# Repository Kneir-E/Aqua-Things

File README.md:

- **Aqua_Things_V2**
  - Arduino IDE platform  
  - Contains the latest version of the Main Device contents *(this is the latest that I can find, I lost copy to the actual final version)*
- **ESP8266_Calibration-Module**
  - Arduino IDE platform  
  - Contains the code for the Calibration Module
- **KiCad Files**
  - **3.1) ESP_Board_Test**  
    - KiCad Schematics for the main board of the device
  - **3.2) ESP8266_Calib_Module**  
    - KiCad Schematics for the calibration module board
  - **3.3) KiCad Extras-Libraries-etc**  
    - Libraries used for the creation of 3.1 and 3.2
- **Ignore the rest of the folders**
- **4) Old Version** → Ignore
- **5) Helper for testing - Lux-Web** → Ignore
- **6) Helper for testing - Temperature-Web** → Ignore

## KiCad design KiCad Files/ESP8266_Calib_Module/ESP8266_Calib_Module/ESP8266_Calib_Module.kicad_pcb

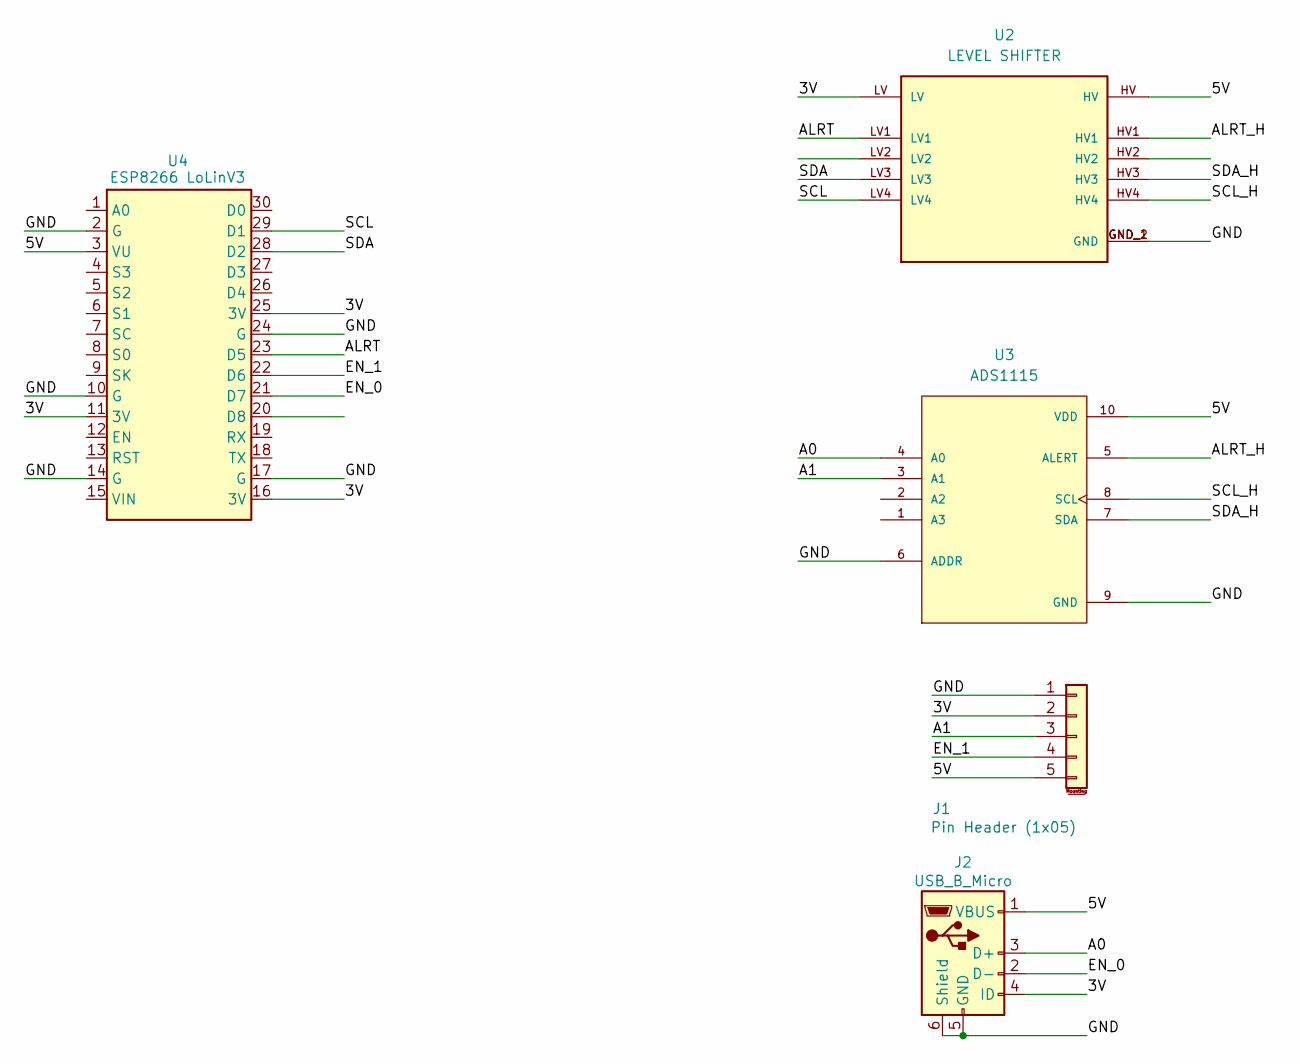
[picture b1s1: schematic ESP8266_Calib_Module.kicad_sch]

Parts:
J1: Pin Header (1x05); PinHeader_1x05_P2.54mm_Vertical
J2: USB_B_Micro; USB_Micro-B_Amphenol_10118194_Horizontal
U2: LEVEL SHIFTER; CONV_BOB-12009; PARTREV 01
U3: ADS1115; MODULE_ZC261500; PARTREV NA
U4: ESP8266 LoLinV3; NodeMCU-LoLinV3

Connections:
/3V: J1.2, J2.4 (ID), U2.LV, U4.11 (3V), U4.16 (3V), U4.25 (3V)
/5V: J1.5, J2.1 (VBUS), U2.HV, U3.10 (VDD), U4.3 (VU)
/A0: J2.3 (D+), U3.4 (A0)
/A1: J1.3, U3.3 (A1)
/ALRT: U2.LV1, U4.23 (D5)
/ALRT_H: U2.HV1, U3.5 (ALERT)
/EN_0: J2.2 (D-), U4.21 (D7)
/EN_1: J1.4, U4.22 (D6)
/GND: J1.1, J2.5 (GND), J2.6 (Shield), U2.GND_1 (GND), U2.GND_2 (GND), U3.6 (ADDR), U3.9 (GND), U4.2 (G), U4.10 (G), U4.14 (G), U4.17 (G), U4.24 (G)
/SCL: U2.LV4, U4.29 (D1)
/SCL_H: U2.HV4, U3.8 (SCL)
/SDA: U2.LV3, U4.28 (D2)
/SDA_H: U2.HV3, U3.7 (SDA)

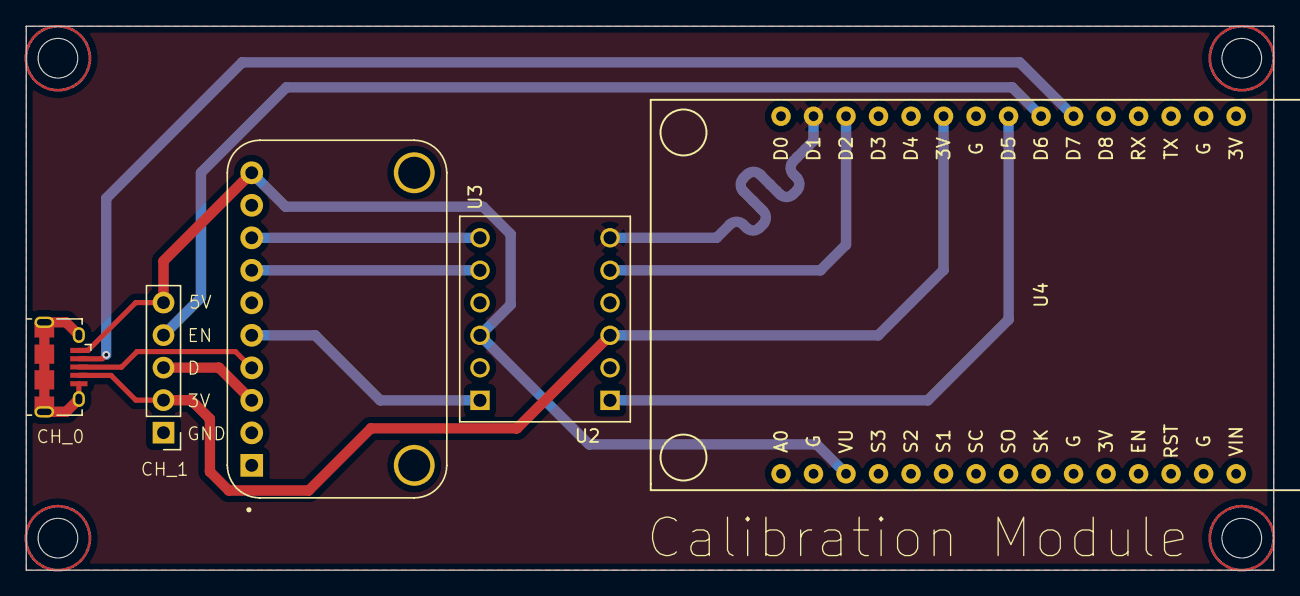
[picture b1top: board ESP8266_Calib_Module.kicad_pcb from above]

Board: 2 copper layers, 97.5 x 42.5 mm, 5 parts (0 on the bottom side), 13 nets.

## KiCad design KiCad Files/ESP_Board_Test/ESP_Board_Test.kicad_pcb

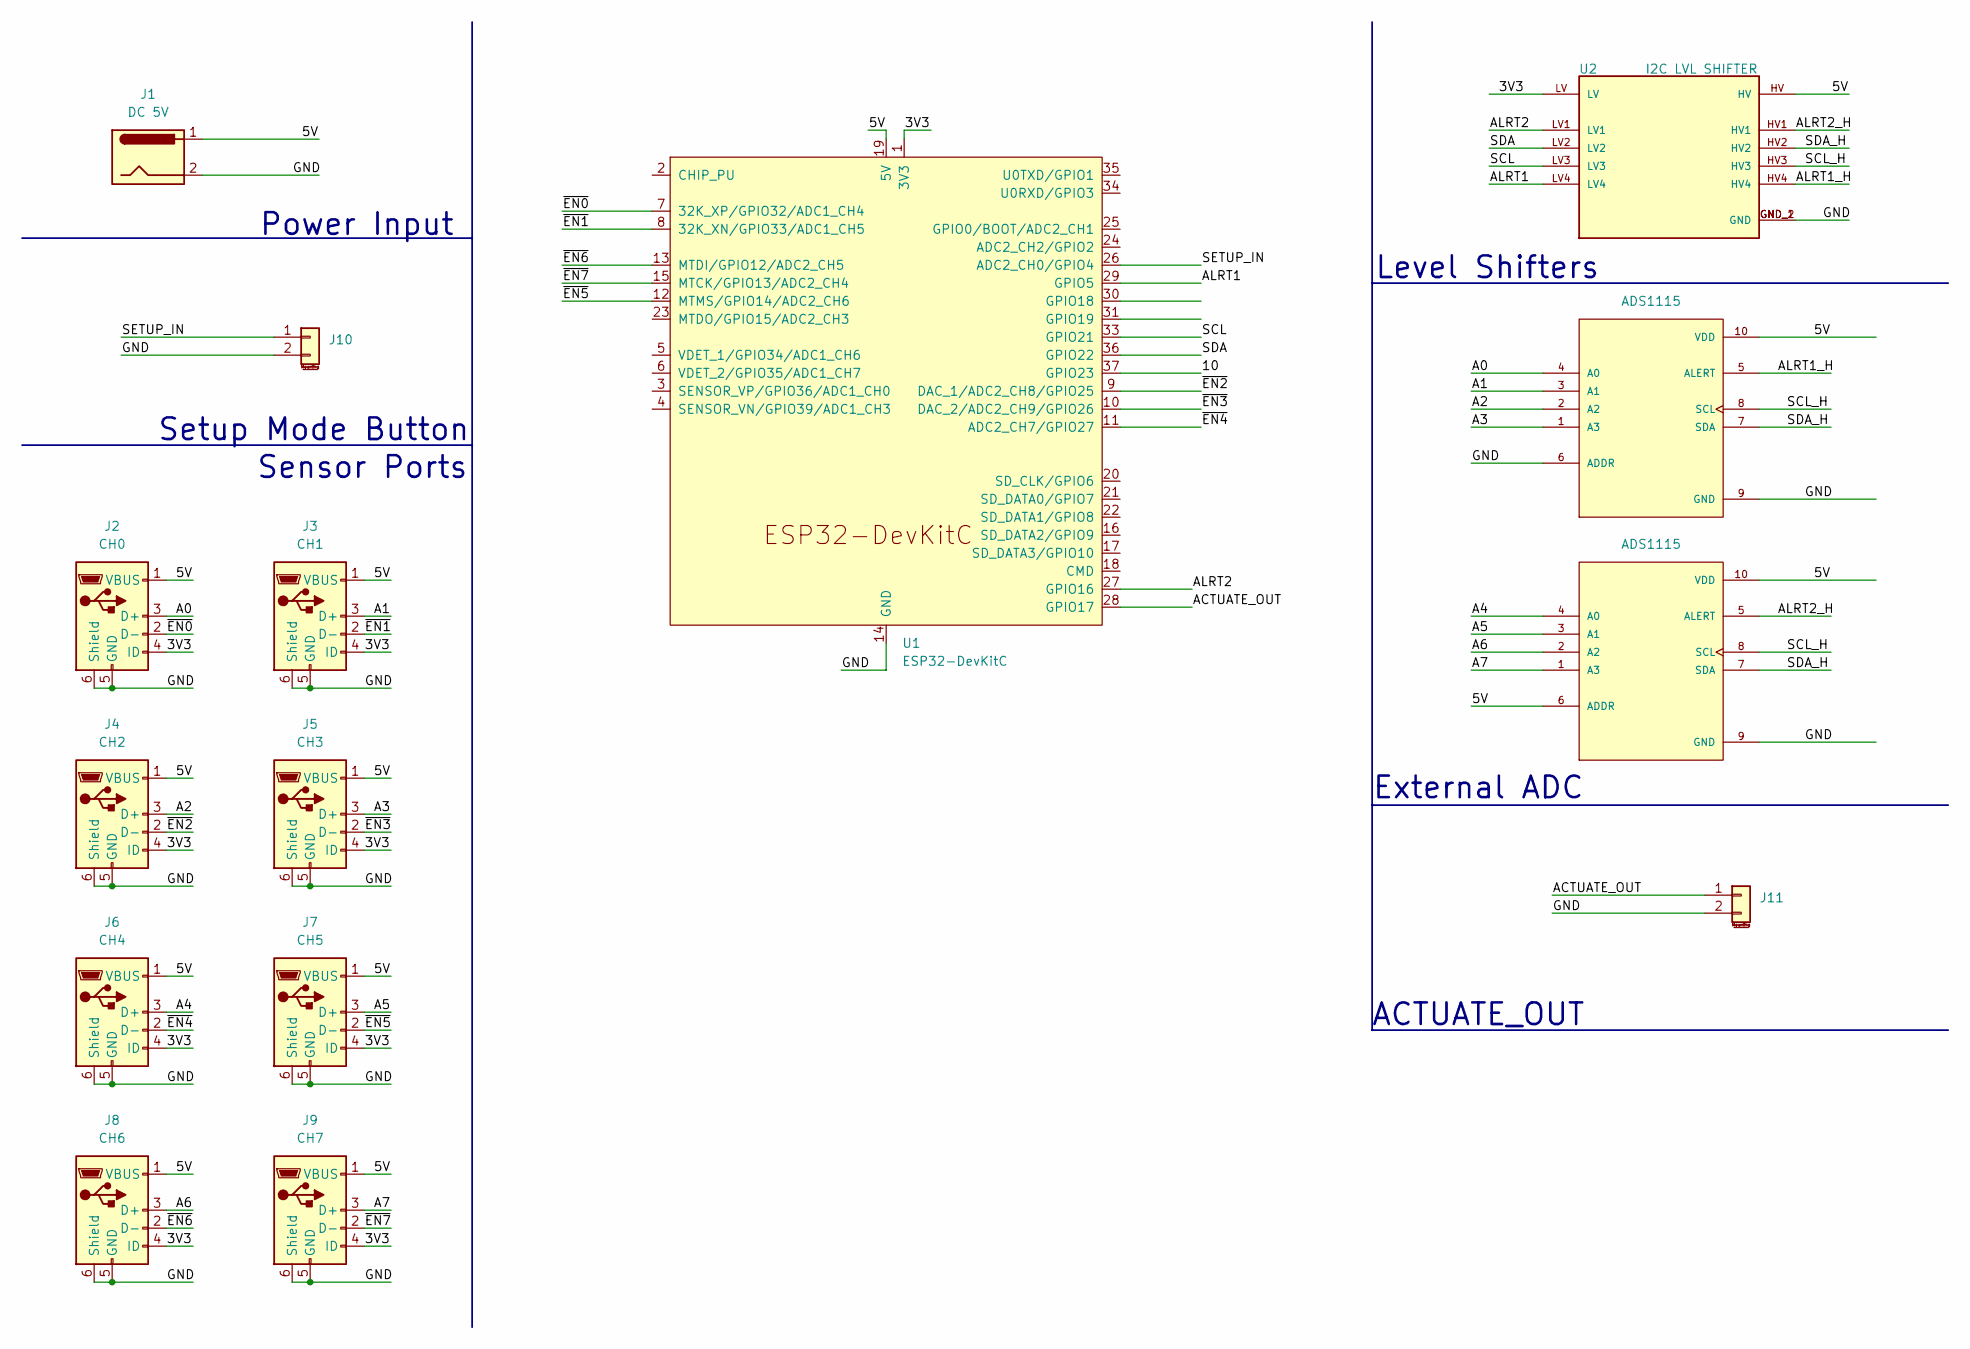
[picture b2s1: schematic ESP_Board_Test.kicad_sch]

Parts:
J1: DC 5V; BarrelJack_Horizontal
J2: CH0; USB_Micro-B_Amphenol_10118194_Horizontal
J3: CH1; USB_Micro-B_Amphenol_10118194_Horizontal
J4: CH2; USB_Micro-B_Amphenol_10118194_Horizontal
J5: CH3; USB_Micro-B_Amphenol_10118194_Horizontal
J6: CH4; USB_Micro-B_Amphenol_10118194_Horizontal
J7: CH5; USB_Micro-B_Amphenol_10118194_Horizontal
J8: CH6; USB_Micro-B_Amphenol_10118194_Horizontal
J9: CH7; USB_Micro-B_Amphenol_10118194_Horizontal
J10, J11: Pin Header; PinHeader_1x02_P2.54mm_Vertical
U1: ESP32-DevKitC
U2: I2C LVL SHIFTER; CONV_BOB-12009; PARTREV 01
U4, U5: ADS1115; MODULE_ZC261500; PARTREV NA

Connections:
/3V3: J2.4 (ID), J3.4 (ID), J4.4 (ID), J5.4 (ID), J6.4 (ID), J7.4 (ID), J8.4 (ID), J9.4 (ID), U1.1 (3V3), U2.LV
/5V: J1.1, J2.1 (VBUS), J3.1 (VBUS), J4.1 (VBUS), J5.1 (VBUS), J6.1 (VBUS), J7.1 (VBUS), J8.1 (VBUS), J9.1 (VBUS), U1.19 (5V), U2.HV, U4.10 (VDD), U5.6 (ADDR), U5.10 (VDD)
/10: U1.37 (GPIO23)
/A0: J2.3 (D+), U4.4 (A0)
/A1: J3.3 (D+), U4.3 (A1)
/A2: J4.3 (D+), U4.2 (A2)
/A3: J5.3 (D+), U4.1 (A3)
/A4: J6.3 (D+), U5.4 (A0)
/A5: J7.3 (D+), U5.3 (A1)
/A6: J8.3 (D+), U5.2 (A2)
/A7: J9.3 (D+), U5.1 (A3)
/ACTUATE_OUT: J11.1, U1.28 (GPIO17)
/ALRT1: U1.29 (GPIO5), U2.LV4
/ALRT1_H: U2.HV4, U4.5 (ALERT)
/ALRT2: U1.27 (GPIO16), U2.LV1
/ALRT2_H: U2.HV1, U5.5 (ALERT)
/GND: J1.2, J2.5 (GND), J2.6 (Shield), J3.5 (GND), J3.6 (Shield), J4.5 (GND), J4.6 (Shield), J5.5 (GND), J5.6 (Shield), J6.5 (GND), J6.6 (Shield), J7.5 (GND), J7.6 (Shield), J8.5 (GND), J8.6 (Shield), J9.5 (GND), J9.6 (Shield), J10.2, J11.2, U1.14 (GND), U1.32 (GND), U1.38 (GND), U2.GND_1 (GND), U2.GND_2 (GND), U4.6 (ADDR), U4.9 (GND), U5.9 (GND)
/SCL: U1.33 (GPIO21), U2.LV3
/SCL_H: U2.HV3, U4.8 (SCL), U5.8 (SCL)
/SDA: U1.36 (GPIO22), U2.LV2
/SDA_H: U2.HV2, U4.7 (SDA), U5.7 (SDA)
/SETUP_IN: J10.1, U1.26 (ADC2_CH0/GPIO4)
/~EN0: J2.2 (D-), U1.7 (32K_XP/GPIO32/ADC1_CH4)
/~EN1: J3.2 (D-), U1.8 (32K_XN/GPIO33/ADC1_CH5)
/~EN2: J4.2 (D-), U1.9 (DAC_1/ADC2_CH8/GPIO25)
/~EN3: J5.2 (D-), U1.10 (DAC_2/ADC2_CH9/GPIO26)
/~EN4: J6.2 (D-), U1.11 (ADC2_CH7/GPIO27)
/~EN5: J7.2 (D-), U1.12 (MTMS/GPIO14/ADC2_CH6)
/~EN6: J8.2 (D-), U1.13 (MTDI/GPIO12/ADC2_CH5)
/~EN7: J9.2 (D-), U1.15 (MTCK/GPIO13/ADC2_CH4)

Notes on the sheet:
Sensor Ports
Power Input
ACTUATE_OUT
External ADC
Level Shifters
Setup Mode Button

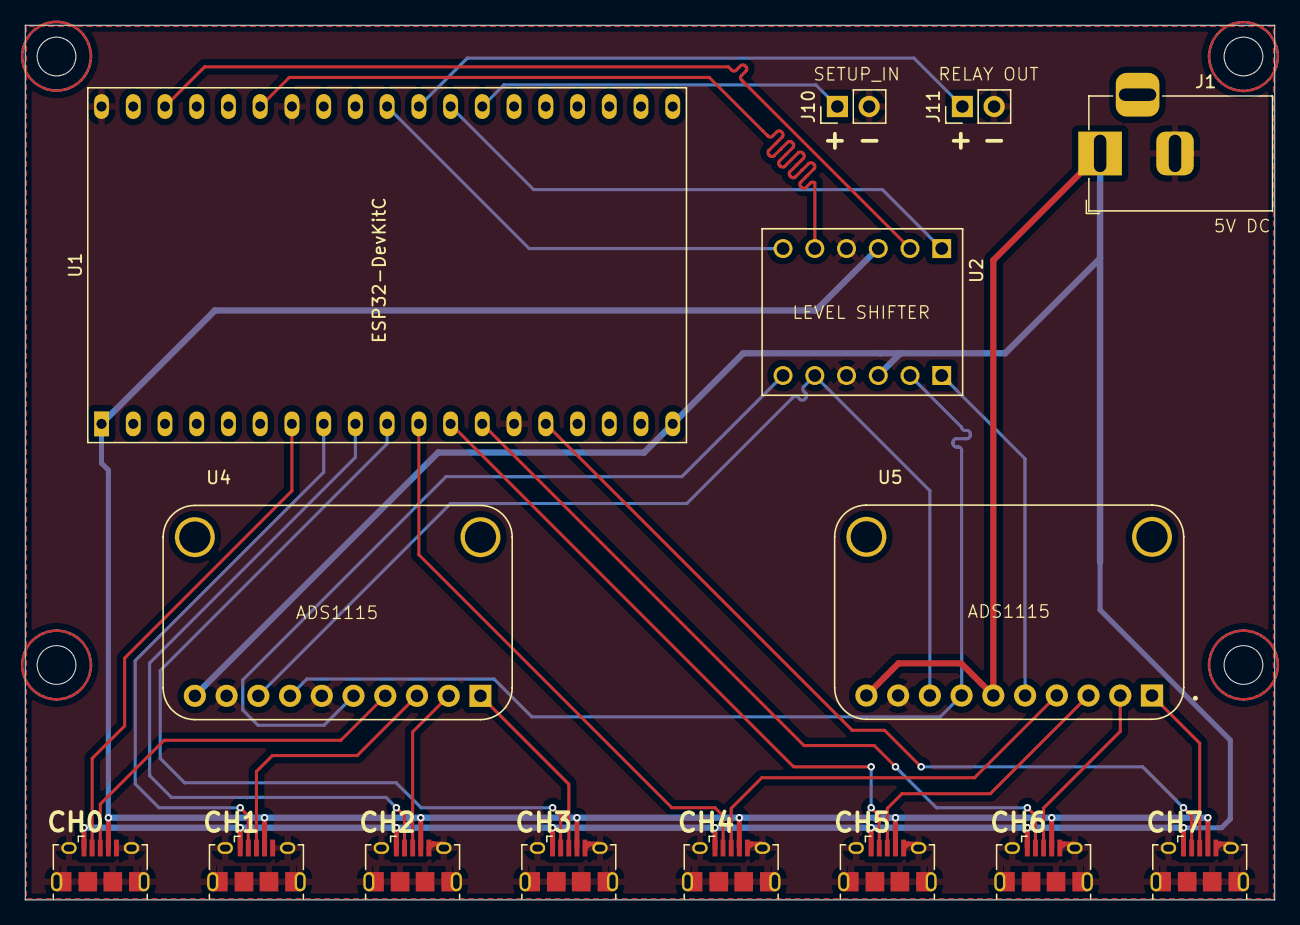
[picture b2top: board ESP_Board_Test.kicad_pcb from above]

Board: 2 copper layers, 100.0 x 70.0 mm, 15 parts (0 on the bottom side), 29 nets.

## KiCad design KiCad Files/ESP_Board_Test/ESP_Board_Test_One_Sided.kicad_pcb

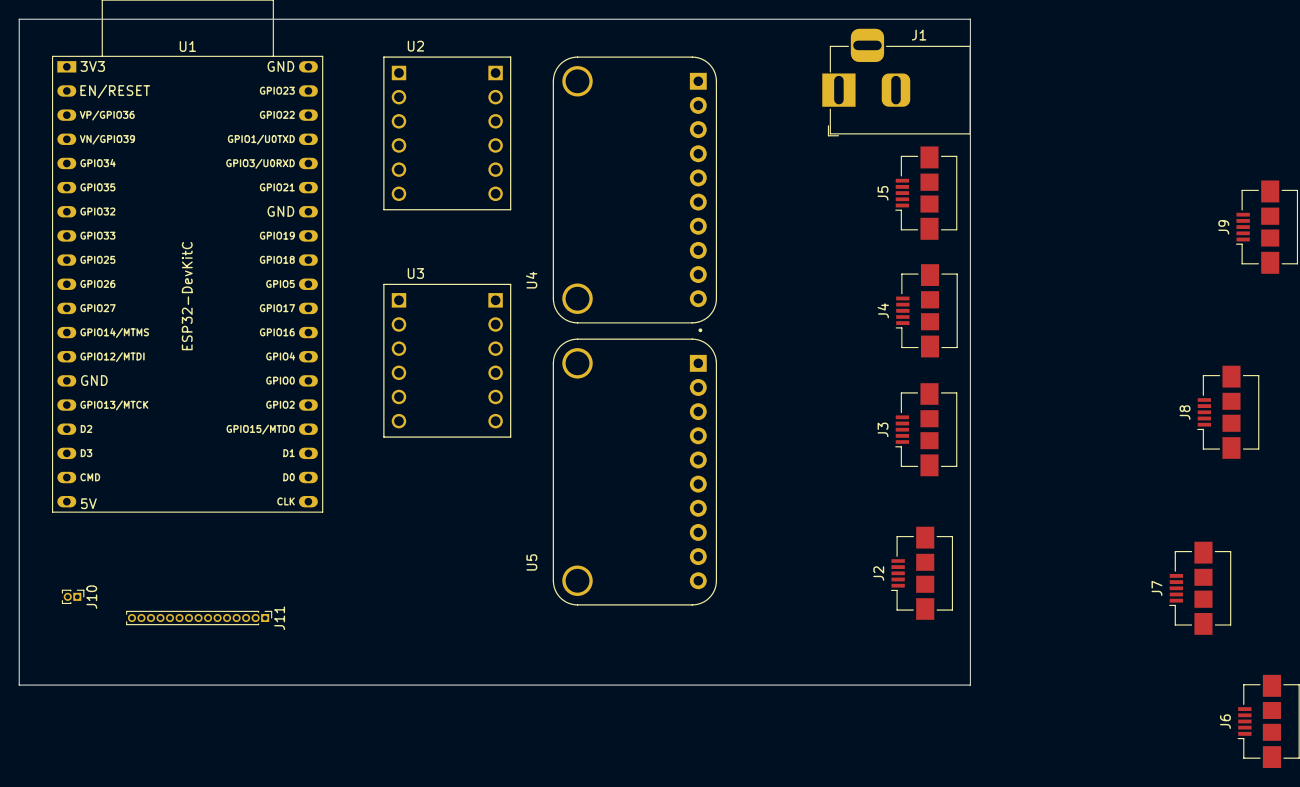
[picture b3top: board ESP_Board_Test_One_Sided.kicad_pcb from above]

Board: 2 copper layers, 100.0 x 70.0 mm, 16 parts (0 on the bottom side), 34 nets, no tracks yet.

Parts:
J1: Barrel_Jack; BarrelJack_Horizontal
J2, J3, J4, J5, J6, J7, J8, J9: USB_B_Micro; USB_Micro-B_Amphenol_10104110_Horizontal
J10: Conn_01x02_MountingPin; PinHeader_1x02_P1.00mm_Vertical
J11: Conn_01x15_MountingPin; PinHeader_1x15_P1.00mm_Vertical
U1: ESP32-DevKitC
U2, U3: BOB-12009; CONV_BOB-12009
U4, U5: ZC261500; MODULE_ZC261500

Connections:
/1: J11.15, U1.7 (32K_XP/GPIO32/ADC1_CH4)
/2: J11.14, U1.8 (32K_XN/GPIO33/ADC1_CH5)
/3: J11.13, U1.13 (MTDI/GPIO12/ADC2_CH5)
/3V3: J2.1 (VBUS), J3.1 (VBUS), J4.1 (VBUS), J5.1 (VBUS), J6.1 (VBUS), J7.1 (VBUS), J8.1 (VBUS), J9.1 (VBUS), U1.1 (3V3), U2.LV, U3.LV
/4: J11.12, U1.15 (MTCK/GPIO13/ADC2_CH4)
/5: J11.11, U1.12 (MTMS/GPIO14/ADC2_CH6)
/5V: J1.1, J2.2 (D-), J3.2 (D-), J4.2 (D-), J5.2 (D-), J6.2 (D-), J7.2 (D-), J8.2 (D-), J9.2 (D-), U1.19 (5V), U2.HV, U3.HV, U4.10 (VDD), U5.10 (VDD)
/6: J11.10, U1.26 (ADC2_CH0/GPIO4)
/7: J11.9, U1.29 (GPIO5)
/8: J11.8, U1.30 (GPIO18)
/9: J11.7, U1.31 (GPIO19)
/10: J11.6, U1.37 (GPIO23)
/11: J11.5, U1.9 (DAC_1/ADC2_CH8/GPIO25)
/12: J11.4, U1.10 (DAC_2/ADC2_CH9/GPIO26)
/13: J11.3, U1.11 (ADC2_CH7/GPIO27)
/14: J11.2, U1.27 (GPIO16)
/15: J11.1, U1.28 (GPIO17)
/A0: J2.3 (D+), U4.4 (A0)
/A1: J3.3 (D+), U4.3 (A1)
/A2: J4.3 (D+), U4.2 (A2)
/A3: J5.3 (D+), U4.1 (A3)
/A4: J6.3 (D+), U5.4 (A0)
/A5: J7.3 (D+), U5.3 (A1)
/A6: J8.3 (D+), U5.2 (A2)
/A7: J9.3 (D+), U5.1 (A3)
/ADDR1_H: U2.HV2, U4.6 (ADDR)
/ADDR2_H: U3.HV4, U5.6 (ADDR)
/ALRT1_H: U2.HV1, U4.5 (ALERT)
/ALRT2_H: U3.HV3, U5.5 (ALERT)
/GND: J1.2, J2.5 (GND), J3.5 (GND), J4.5 (GND), J5.5 (GND), J6.5 (GND), J7.5 (GND), J8.5 (GND), J9.5 (GND), J10.2, U1.14 (GND), U1.32 (GND), U1.38 (GND), U2.GND_1 (GND), U2.GND_2 (GND), U3.GND_1 (GND), U3.GND_2 (GND), U4.9 (GND), U5.9 (GND)
/SCL: U1.33 (GPIO21), U3.LV2
/SCL_H: U3.HV2, U4.8 (SCL), U5.8 (SCL)
/SDA: U1.36 (GPIO22), U3.LV1
/SDA_H: U3.HV1, U4.7 (SDA), U5.7 (SDA)

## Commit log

2024-09-10 Initial Commit
    Uploaded Calibration Module and Main Unit
2025-09-18 V2 and Calibration Module Update
2025-09-18 Hardware FIles
